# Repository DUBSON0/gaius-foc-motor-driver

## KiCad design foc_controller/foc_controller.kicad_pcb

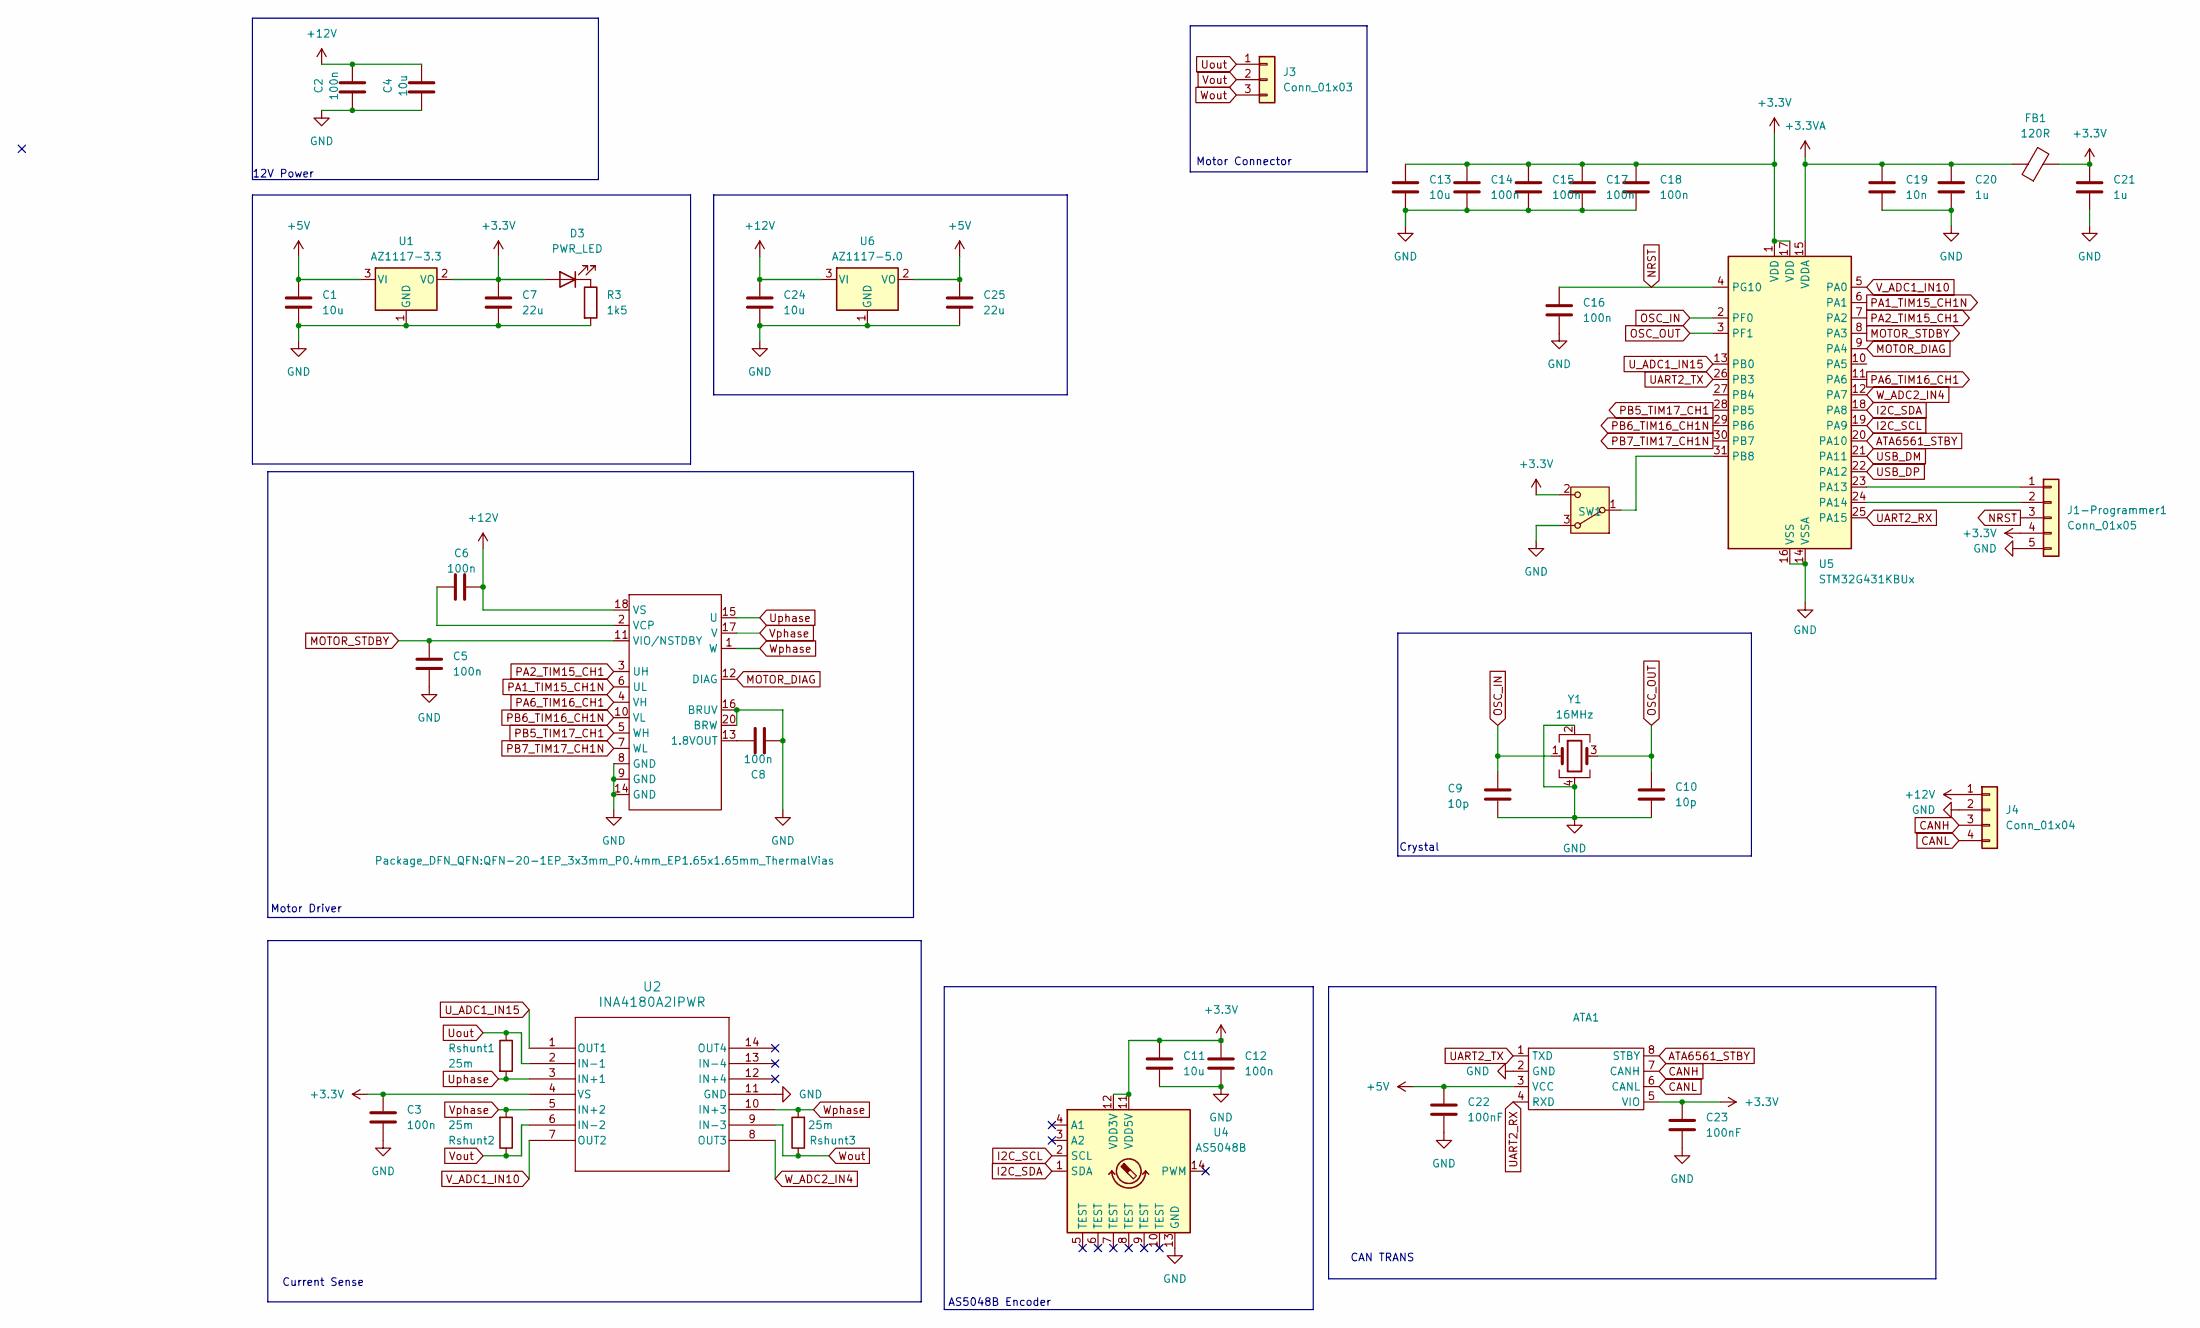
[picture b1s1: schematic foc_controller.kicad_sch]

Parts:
ATA1: DFN-8-1EP_3x3mm_P0.5mm_EP1.65x2.38mm
C1, C4, C11, C13, C24: 10u; C_0603_1608Metric
C2, C3, C5, C6, C8, C12, C14, C15, C16, C17, C18: 100n; C_0603_1608Metric
C7, C25: 22u; C_0603_1608Metric
C9, C10: 10p; C_0603_1608Metric
C19: 10n; C_0603_1608Metric
C20, C21: 1u; C_0603_1608Metric
C22, C23: 100nF; C_0603_1608Metric
D3: PWR_LED; LED_0603_1608Metric
FB1: 120R; L_0603_1608Metric
J1-Programmer1: Conn_01x05; PinHeader_1x05_P1.27mm_Vertical
J3: Conn_01x03; PinHeader_1x03_P2.00mm_Vertical
J4: Conn_01x04; PinHeader_1x04_P2.00mm_Vertical
R3: 1k5; R_0603_1608Metric
Rshunt1, Rshunt2, Rshunt3: 25m; R_0603_1608Metric
SW1: SMT_FS
U1: AZ1117-3.3; SOT-223_DIO
U2: INA4180A2IPWR; PW14_TEX
U3: QFN-20-1EP_3x3mm_P0.4mm_EP1.65x1.65mm_ThermalVias
U4: AS5048B; TSSOP-14_4.4x5mm_P0.65mm
U5: STM32G431KBUx; QFN-32-1EP_5x5mm_P0.5mm_EP3.45x3.45mm
U6: AZ1117-5.0; SOT-223_DIO
Y1: 16MHz; XTAL_ABM10AIG-16.000MHZ-4Z-T3

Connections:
+3.3V: ATA1.5 (VIO), C3.1, C7.1, C11.1, C12.1, C13.1, C14.1, C15.1, C17.1, C18.1, C21.1, C23.1, D3.2 (A), FB1.2, J1-Programmer1.4, SW1.2 (C), U1.2 (VO), U2.4 (VS), U4.11 (VDD5V), U4.12 (VDD3V), U5.1 (VDD), U5.17 (VDD)
+3.3VA: C19.1, C20.1, FB1.1, U5.15 (VDDA)
+5V: ATA1.3 (VCC), C1.1, C22.1, C25.1, U1.3 (VI), U6.2 (VO)
+12V: C2.1, C4.1, C6.1, C24.1, J4.1, U3.18 (VS), U6.3 (VI)
ATA6561_STBY: ATA1.8 (STBY), U5.20 (PA10)
CANH: ATA1.7 (CANH), J4.3
CANL: ATA1.6 (CANL), J4.4
GND: ATA1.2 (GND), C1.2, C2.2, C3.2, C4.2, C5.2, C7.2, C8.2, C9.2, C10.2, C11.2, C12.2, C13.2, C14.2, C15.2, C16.2, C17.2, C18.2, C19.2, C20.2, C21.2, C22.2, C23.2, C24.2, C25.2, J1-Programmer1.5, J4.2, R3.2, SW1.3 (A), U1.1 (GND), U2.11 (GND), U3.8 (GND), U3.9 (GND), U3.14 (GND), U3.16 (BRUV), U3.20 (BRW), U4.13 (GND), U5.14 (VSSA), U5.16 (VSS), U5.32 (VSS), U5.33 (VSS), U6.1 (GND), Y1.2, Y1.4
I2C_SCL: U4.2 (SCL), U5.19 (PA9)
I2C_SDA: U4.1 (SDA), U5.18 (PA8)
MOTOR_DIAG: U3.12 (DIAG), U5.9 (PA4)
MOTOR_STDBY: C5.1, U3.11 (VIO/NSTDBY), U5.8 (PA3)
NRST: C16.1, J1-Programmer1.3, U5.4 (PG10)
unnamed: D3.1 (K), R3.1
unnamed: J1-Programmer1.1, U5.23 (PA13)
unnamed: J1-Programmer1.2, U5.24 (PA14)
unnamed: SW1.1 (B), U5.31 (PB8)
unnamed: C8.1, U3.13 (1.8VOUT)
unnamed: C6.2, U3.2 (VCP)
OSC_IN: C9.1, U5.2 (PF0), Y1.1
OSC_OUT: C10.1, U5.3 (PF1), Y1.3
PA1_TIM15_CH1N: U3.6 (UL), U5.6 (PA1)
PA2_TIM15_CH1: U3.3 (UH), U5.7 (PA2)
PA6_TIM16_CH1: U3.4 (VH), U5.11 (PA6)
PB5_TIM17_CH1: U3.5 (WH), U5.28 (PB5)
PB6_TIM16_CH1N: U3.10 (VL), U5.29 (PB6)
PB7_TIM17_CH1N: U3.7 (WL), U5.30 (PB7)
UART2_RX: ATA1.4 (RXD), U5.25 (PA15)
UART2_TX: ATA1.1 (TXD), U5.26 (PB3)
USB_DM: U5.21 (PA11)
USB_DP: U5.22 (PA12)
U_ADC1_IN15: U2.1 (OUT1), U5.13 (PB0)
Uout: J3.1, Rshunt1.1, U2.2 (IN-1)
Uphase: Rshunt1.2, U2.3 (IN+1), U3.15 (U)
V_ADC1_IN10: U2.7 (OUT2), U5.5 (PA0)
Vout: J3.2, Rshunt2.1, U2.6 (IN-2)
Vphase: Rshunt2.2, U2.5 (IN+2), U3.17 (V)
W_ADC2_IN4: U2.8 (OUT3), U5.12 (PA7)
Wout: J3.3, Rshunt3.1, U2.9 (IN-3)
Wphase: Rshunt3.2, U2.10 (IN+3), U3.1 (W)

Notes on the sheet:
AS5048B Encoder
12V Power
Current Sense
Motor Connector
Motor Driver
Crystal
CAN TRANS

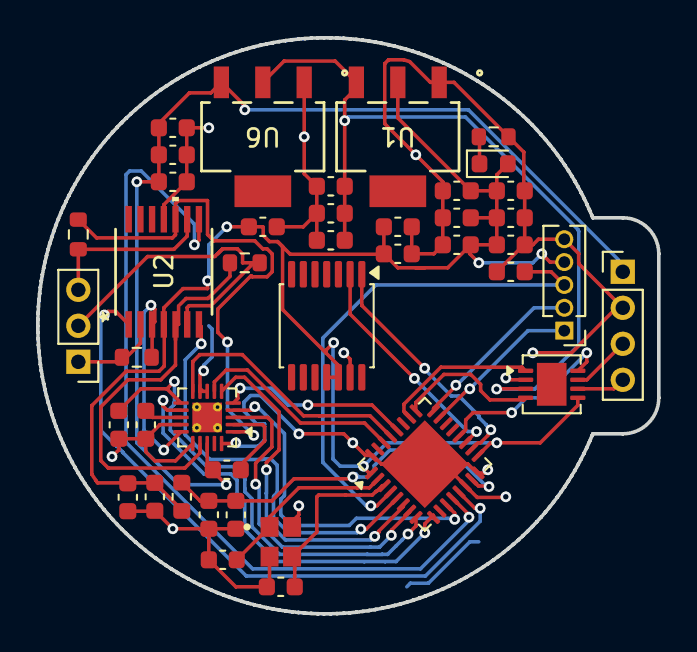
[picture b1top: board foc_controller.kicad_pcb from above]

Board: 2 copper layers, 34.5 x 32.0 mm, 42 parts (0 on the bottom side), 37 nets.

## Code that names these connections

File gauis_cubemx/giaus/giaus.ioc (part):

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Mcu.Name=STM32G431K(6-8-B)Ux
Mcu.Package=UFQFPN32
Mcu.UserName=STM32G431KBUx
PA0.Mode=IN1-Single-Ended
PA0.Signal=ADC1_IN1
PA1.Mode=PWM Generation1 CH1 CH1N
PA1.Signal=TIM15_CH1N
PA11.Mode=Device
PA11.Signal=USB_DM
PA12.Mode=Device
PA12.Signal=USB_DP
PA13.Mode=Serial_Wire
PA13.Signal=SYS_JTMS-SWDIO
PA14.Mode=Serial_Wire
PA14.Signal=SYS_JTCK-SWCLK
PA15.Mode=Asynchronous
PA15.Signal=USART2_RX
PA2.Signal=S_TIM15_CH1
PA3.Signal=GPIO_Output
PA4.Signal=GPIO_Input
PA6.Signal=S_TIM16_CH1
PA7.Mode=IN4-Single-Ended
PA7.Signal=ADC2_IN4
PA8.Mode=I2C
PA8.Signal=I2C2_SDA
PA9.Mode=I2C
PA9.Signal=I2C2_SCL
PB0.Mode=IN15-Single-Ended
PB0.Signal=ADC1_IN15
PB3.Mode=Asynchronous
PB3.Signal=USART2_TX
PB5.Signal=S_TIM17_CH1
PB6.Mode=Output Compare1 CH1 CH1N
PB6.Signal=TIM16_CH1N
PB7.Mode=Output Compare1 CH1 CH1N
PB7.Signal=TIM17_CH1N
PF0-OSC_IN.Mode=HSE-External-Oscillator
PF0-OSC_IN.Signal=RCC_OSC_IN
PF1-OSC_OUT.Mode=HSE-External-Oscillator
PF1-OSC_OUT.Signal=RCC_OSC_OUT
RCC.HSE_VALUE=8000000
RCC.SYSCLKFreq_VALUE=16000000
board=custom

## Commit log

2025-10-24 Init commit
2025-10-25 Pcb nearly complete
2025-10-25 Polish
2025-10-25 Finalized first version
2025-10-31 Added ATA6561 footprints
2025-11-04 Circular rendition started.
2025-11-04 More routing
2025-11-04 Commiting again
2025-11-05 Finished routing
2025-11-07 Considering adding thicker traces for 12v
2025-11-28 Changed a few things I guess?
2025-12-04 cleaning up firstboard
2026-01-29 House cleaning
2026-03-18 Update KiCad project settings and backups
